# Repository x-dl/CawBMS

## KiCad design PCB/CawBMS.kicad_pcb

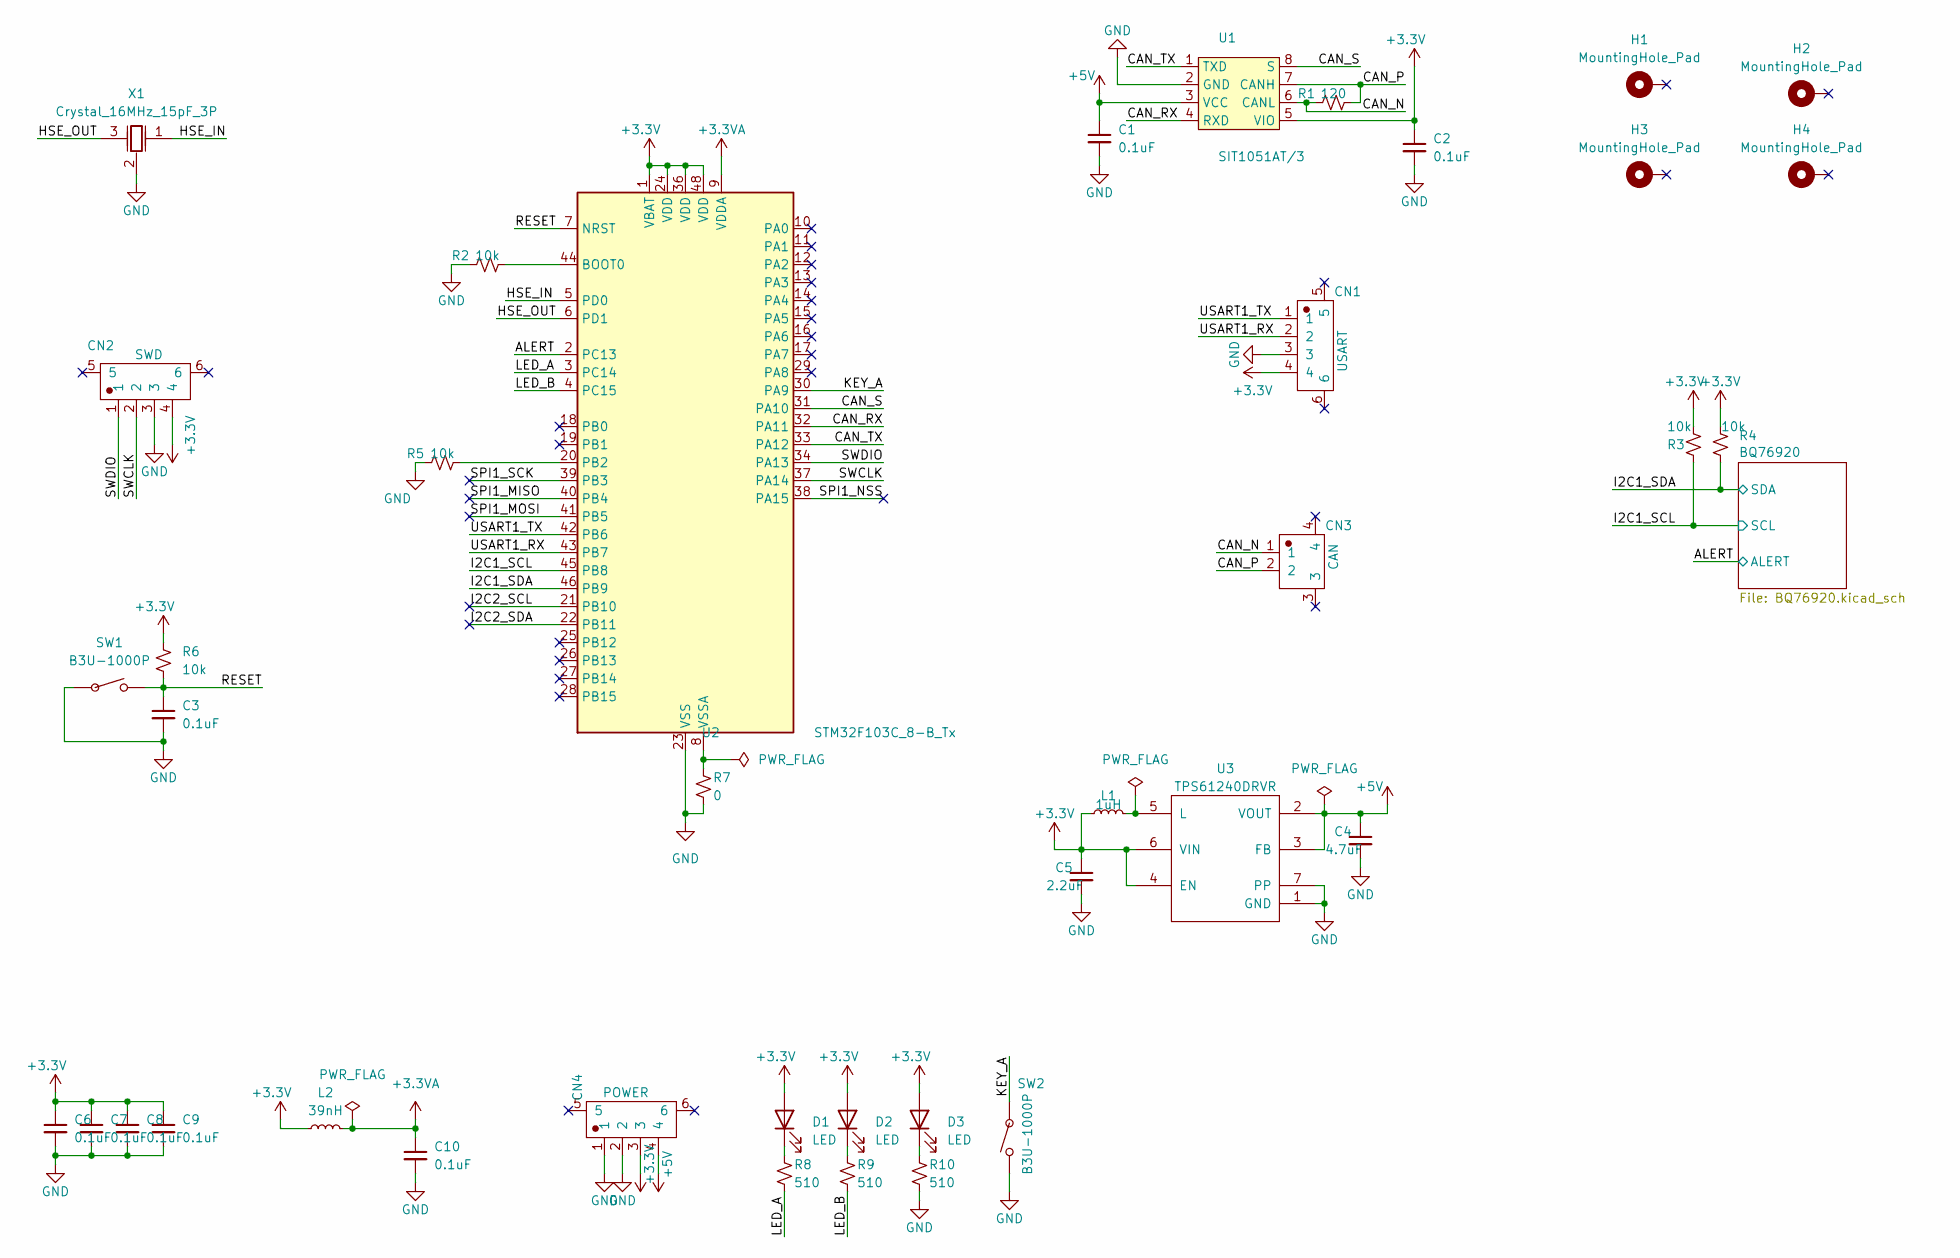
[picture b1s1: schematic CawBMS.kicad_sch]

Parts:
C1, C2, C3, C6, C7, C8, C9, C10: 0.1uF; C_0402_1005Metric_Pad0.74x0.62mm_HandSolder
C4: 4.7uF; C_0402_1005Metric_Pad0.74x0.62mm_HandSolder
C5: 2.2uF; C_0402_1005Metric_Pad0.74x0.62mm_HandSolder
CN1: USART; CONN-SMD_4P-P1.00_WAFER-SH1.0-4PWB
CN2: SWD; CONN-SMD_4P-P1.00_WAFER-SH1.0-4PWB
CN3: CAN; CONN-SMD_2P-P1.00_XUNPU_WAFER-SH1.0-2PWB
CN4: POWER; CONN-SMD_4P-P1.00_WAFER-SH1.0-4PWB
D1, D2, D3: LED; LED_0402_1005Metric_Pad0.77x0.64mm_HandSolder
H1, H2, H3, H4: MountingHole_Pad; MountingHole_2.2mm_M2_Pad_Via
L1: 1uH; L_1210_3225Metric_Pad1.42x2.65mm_HandSolder
L2: 39nH; L_0402_1005Metric_Pad0.77x0.64mm_HandSolder
R1: 120; R_0402_1005Metric_Pad0.72x0.64mm_HandSolder
R2, R3, R4, R5, R6: 10k; R_0402_1005Metric_Pad0.72x0.64mm_HandSolder
R7: 0; R_0402_1005Metric_Pad0.72x0.64mm_HandSolder
R8, R9, R10: 510; R_0402_1005Metric_Pad0.72x0.64mm_HandSolder
SW1, SW2: B3U-1000P; JLC Part Number C231329
U1: SIT1051AT/3; ISO1044BDR_SOP-8
U2: STM32F103C_8-B_Tx; LQFP-48_7x7mm_P0.5mm
U3: TPS61240DRVR; TPS61240DRVR_WSON-6_L2.0-W2.0-P0.65-TL-EP
X1: Crystal_16MHz_15pF_3P; Crystal_SMD3213-3P; JLC Part Number C341521

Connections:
+3.3V: C2.1, C5.1, C6.1, C7.1, C8.1, C9.1, CN1.4, CN2.4, CN4.3, D1.2 (A), D2.2 (A), D3.2 (A), L1.1, L2.1, R3.1, R4.1, R6.1, U1.5 (VIO), U2.1 (VBAT), U2.24 (VDD), U2.36 (VDD), U2.48 (VDD), U3.4 (EN), U3.6 (VIN); also elsewhere on the board
+3.3VA: C10.1, L2.2, U2.9 (VDDA)
+5V: C1.1, C4.1, CN4.4, U1.3 (VCC), U3.2 (VOUT), U3.3 (FB)
/ALERT: U2.2 (PC13); also elsewhere on the board
/CAN_N: CN3.1, R1.1, U1.6 (CANL)
/CAN_P: CN3.2, R1.2, U1.7 (CANH)
/CAN_RX: U1.4 (RXD), U2.32 (PA11)
/CAN_S: U1.8 (S), U2.31 (PA10)
/CAN_TX: U1.1 (TXD), U2.33 (PA12)
/HSE_IN: U2.5 (PD0), X1.1 (OSC1)
/HSE_OUT: U2.6 (PD1), X1.3 (OSC2)
/I2C1_SCL: R3.2, U2.45 (PB8); also elsewhere on the board
/I2C1_SDA: R4.2, U2.46 (PB9); also elsewhere on the board
/I2C2_SCL: U2.21 (PB10)
/I2C2_SDA: U2.22 (PB11)
/KEY_A: SW2.1, U2.30 (PA9)
/LED_A: R8.2, U2.3 (PC14)
/LED_B: R9.2, U2.4 (PC15)
/RESET: C3.1, R6.2, SW1.2, U2.7 (NRST)
/SPI1_MISO: U2.40 (PB4)
/SPI1_MOSI: U2.41 (PB5)
/SPI1_NSS: U2.38 (PA15)
/SPI1_SCK: U2.39 (PB3)
/SWCLK: CN2.2, U2.37 (PA14)
/SWDIO: CN2.1, U2.34 (PA13)
/USART1_RX: CN1.2, U2.43 (PB7)
/USART1_TX: CN1.1, U2.42 (PB6)
GND: C1.2, C2.2, C3.2, C4.2, C5.2, C6.2, C7.2, C8.2, C9.2, C10.2, CN1.3, CN2.3, CN4.1, CN4.2, R2.1, R5.1, R7.2, R10.2, SW1.1, SW2.2, U1.2 (GND), U2.23 (VSS), U2.35 (VSS), U2.47 (VSS), U3.1 (GND), U3.7 (PP), X1.2 (GND); also elsewhere on the board
unnamed: D1.1 (K), R8.1
unnamed: D2.1 (K), R9.1
unnamed: D3.1 (K), R10.1
unnamed: R2.2, U2.44 (BOOT0)
unnamed: R5.2, U2.20 (PB2)
unnamed: R7.1, U2.8 (VSSA)
unnamed: L1.2, U3.5 (L)

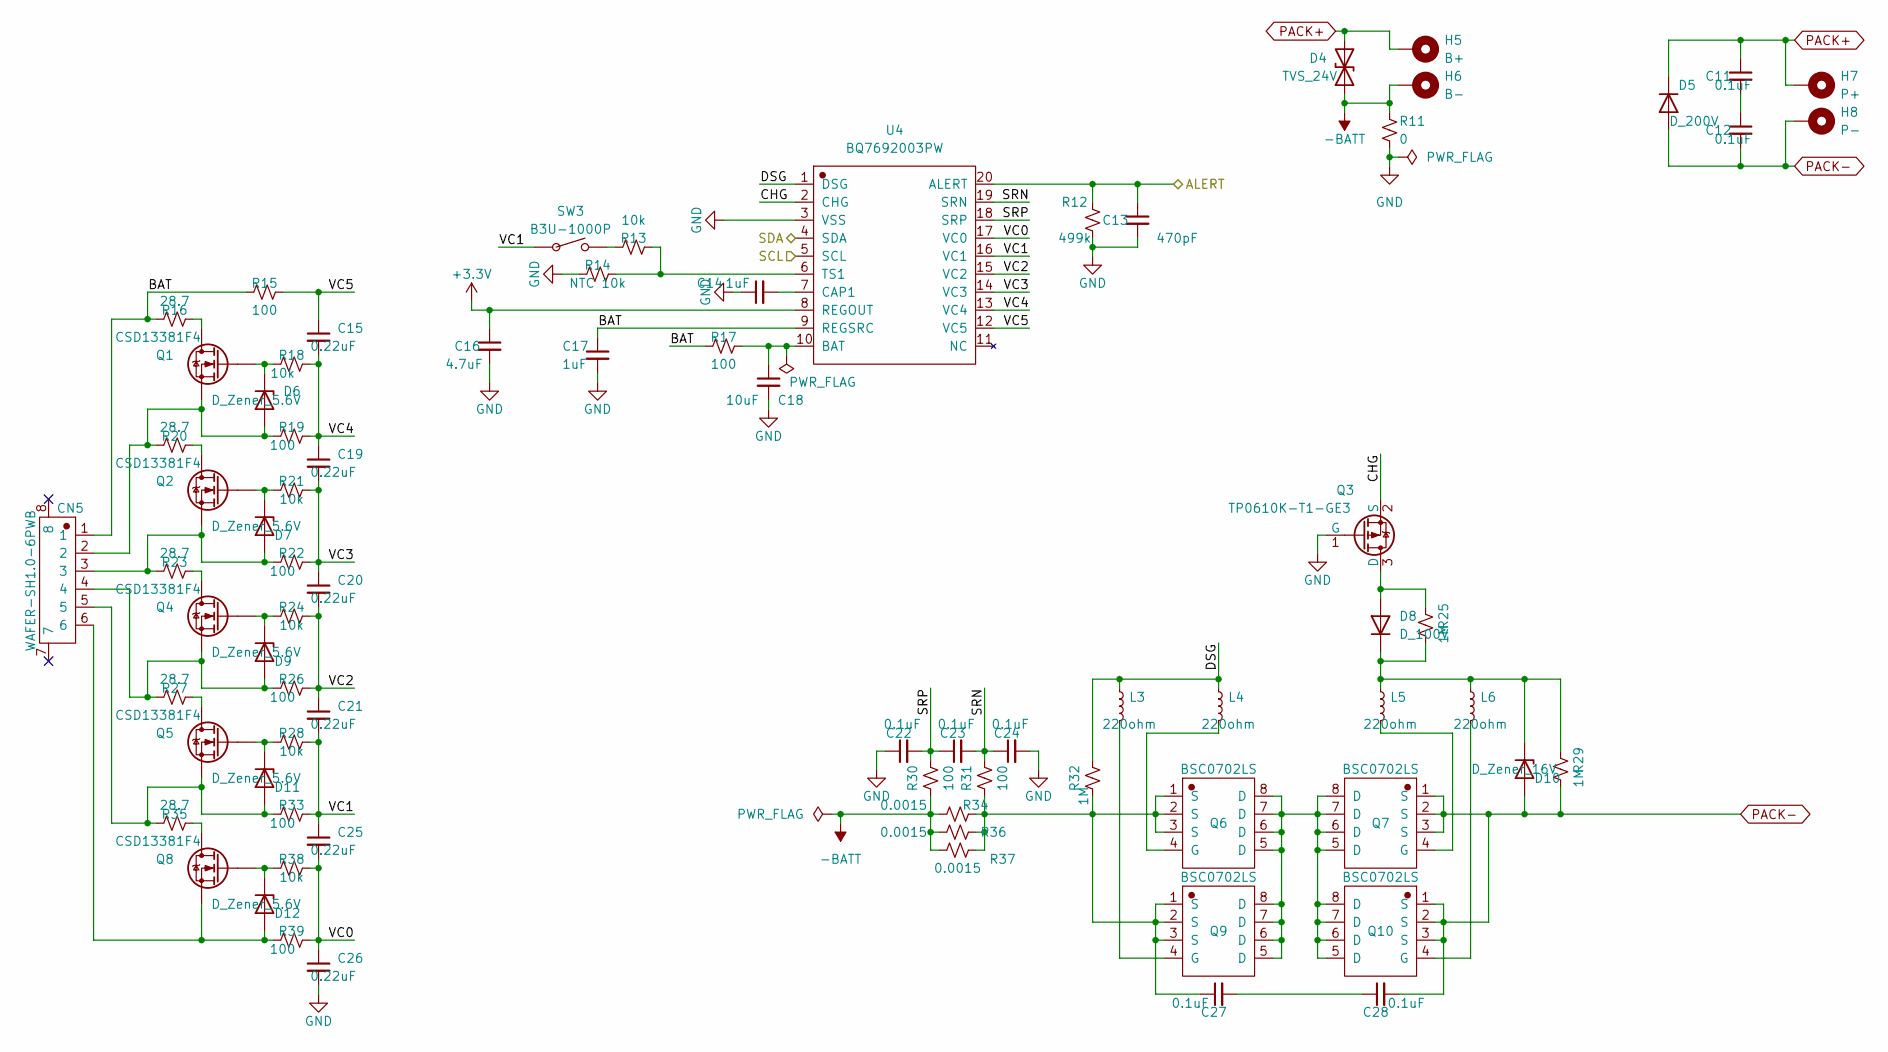
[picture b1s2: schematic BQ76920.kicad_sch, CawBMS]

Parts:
C11, C12, C27, C28: 0.1uF; C_0603_1608Metric_Pad1.08x0.95mm_HandSolder
C13: 470pF; C_0402_1005Metric_Pad0.74x0.62mm_HandSolder
C14, C17: 1uF; C_0402_1005Metric_Pad0.74x0.62mm_HandSolder
C15, C19, C20, C21, C25, C26: 0.22uF; C_0402_1005Metric_Pad0.74x0.62mm_HandSolder
C16: 4.7uF; C_0402_1005Metric_Pad0.74x0.62mm_HandSolder
C18: 10uF; C_0603_1608Metric_Pad1.08x0.95mm_HandSolder
C22, C23, C24: 0.1uF; C_0402_1005Metric_Pad0.74x0.62mm_HandSolder
CN5: WAFER-SH1.0-6PWB; CONN-SMD_6P-P1.00_XUNPU_WAFER-SH1.0-6PWB
D4: TVS_24V; D_SMA_Handsoldering
D5: D_200V; D_SMA_Handsoldering
D6, D7, D9, D11, D12: D_Zener_5.6V; D_SOD-523
D8: D_100V; D_SOD-323_HandSoldering
D10: D_Zener_16V; D_SOD-523
H5: B+; POWER_PAD
H6: B-; POWER_PAD
H7: P+; POWER_PAD
H8: P-; POWER_PAD
L3, L4, L5, L6: 220ohm; L_0603_1608Metric_Pad1.05x0.95mm_HandSolder
Q1, Q2, Q4, Q5, Q8: CSD13381F4; CSD13381F4_PICOSTAR-3_L1.0-W0.6-P0.40-S0.65-BL-1
Q3: TP0610K-T1-GE3; SOT-23
Q6, Q7, Q9, Q10: BSC0702LS; BSC0702LS_PG-TDSON-8_L5.0-W6.0-P1.27-BL-EP
R11: 0; R_0402_1005Metric_Pad0.72x0.64mm_HandSolder
R12: 499k; R_0402_1005Metric_Pad0.72x0.64mm_HandSolder
R13, R18, R21, R24, R28, R38: 10k; R_0402_1005Metric_Pad0.72x0.64mm_HandSolder
R14: NTC 10k; R_0402_1005Metric_Pad0.72x0.64mm_HandSolder
R15, R17, R19, R22, R26, R30, R31, R33, R39: 100; R_0402_1005Metric_Pad0.72x0.64mm_HandSolder
R16, R20, R23, R27, R35: 28.7; R_0402_1005Metric_Pad0.72x0.64mm_HandSolder
R25, R29, R32: 1M; R_0402_1005Metric_Pad0.72x0.64mm_HandSolder
R34, R36, R37: 0.0015; R_2512_6332Metric_Pad1.40x3.35mm_HandSolder
SW3: B3U-1000P; JLC Part Number C231329
U4: BQ7692003PW; BQ7692003PW_TSSOP-20_L6.5-W4.4-P0.65-LS6.4-BL

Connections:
+3.3V: C16.1, U4.8 (REGOUT); also elsewhere on the board
-BATT: D4.1 (A1), H6.1, R11.1, R30.1, R34.1, R36.1, R37.1
/ALERT: C13.1, R12.2, U4.20 (ALERT); also elsewhere on the board
/BQ76920/BAT: C17.1, CN5.1, R15.1, R16.1, R17.1, U4.9 (REGSRC)
/BQ76920/CHG: Q3.2 (S), U4.2 (CHG)
/BQ76920/DSG: L3.1, L4.1, R32.2, U4.1 (DSG)
/BQ76920/SRN: C23.2, C24.1, R31.2, U4.19 (SRN)
/BQ76920/SRP: C22.2, C23.1, R30.2, U4.18 (SRP)
/BQ76920/VC0: C25.2, C26.1, R38.2, R39.2, U4.17 (VC0)
/BQ76920/VC1: C21.2, C25.1, R28.2, R33.2, SW3.1, U4.16 (VC1)
/BQ76920/VC2: C20.2, C21.1, R24.2, R26.2, U4.15 (VC2)
/BQ76920/VC3: C19.2, C20.1, R21.2, R22.2, U4.14 (VC3)
/BQ76920/VC4: C15.2, C19.1, R18.2, R19.2, U4.13 (VC4)
/BQ76920/VC5: C15.1, R15.2, U4.12 (VC5)
/I2C1_SCL: U4.5 (SCL); also elsewhere on the board
/I2C1_SDA: U4.4 (SDA); also elsewhere on the board
GND: C13.2, C14.1, C16.2, C17.2, C18.2, C22.1, C24.2, C26.2, Q3.1 (G), R11.2, R12.1, R14.1, U4.3 (VSS); also elsewhere on the board
unnamed: C11.2, C12.1
unnamed: C27.1, Q6.1 (S), Q6.2 (S), Q6.3 (S), Q9.1 (S), Q9.2 (S), Q9.3 (S), R31.1, R32.1, R34.2, R36.2, R37.2
unnamed: C27.2, C28.1
unnamed: CN5.2, D6.2 (A), Q1.2 (S), R19.1, R20.1
unnamed: D6.1 (K), Q1.1 (G), R18.1
unnamed: CN5.3, D7.2 (A), Q2.2 (S), R22.1, R23.1
unnamed: D7.1 (K), Q2.1 (G), R21.1
unnamed: D8.2 (A), Q3.3 (D), R25.2
unnamed: CN5.4, D9.2 (A), Q4.2 (S), R26.1, R27.1
unnamed: D9.1 (K), Q4.1 (G), R24.1
unnamed: D8.1 (K), D10.1 (K), L5.1, L6.1, R25.1, R29.2
unnamed: CN5.5, D11.2 (A), Q5.2 (S), R33.1, R35.1
unnamed: D11.1 (K), Q5.1 (G), R28.1
unnamed: CN5.6, D12.2 (A), Q8.2 (S), R39.1
unnamed: D12.1 (K), Q8.1 (G), R38.1
unnamed: Q1.3 (D), R16.2
unnamed: Q2.3 (D), R20.2
unnamed: Q4.3 (D), R23.2
unnamed: Q5.3 (D), R27.2
unnamed: L4.2, Q6.4 (G)
unnamed: L5.2, Q7.4 (G)
unnamed: Q8.3 (D), R35.2
unnamed: L3.2, Q9.4 (G)
unnamed: Q6.5 (D), Q6.6 (D), Q6.7 (D), Q6.8 (D), Q7.5 (D), Q7.6 (D), Q7.7 (D), Q7.8 (D), Q9.5 (D), Q9.6 (D), Q9.7 (D), Q9.8 (D), Q10.5 (D), Q10.6 (D), Q10.7 (D), Q10.8 (D)
unnamed: L6.2, Q10.4 (G)
unnamed: R13.1, SW3.2
unnamed: C18.1, R17.2, U4.10 (BAT)
unnamed: C14.2, U4.7 (CAP1)
unnamed: R13.2, R14.2, U4.6 (TS1)
PACK+: C11.1, D4.2 (A2), D5.1 (K), H5.1, H7.1
PACK-: C12.2, C28.2, D5.2 (A), D10.2 (A), H8.1, Q7.1 (S), Q7.2 (S), Q7.3 (S), Q10.1 (S), Q10.2 (S), Q10.3 (S), R29.1

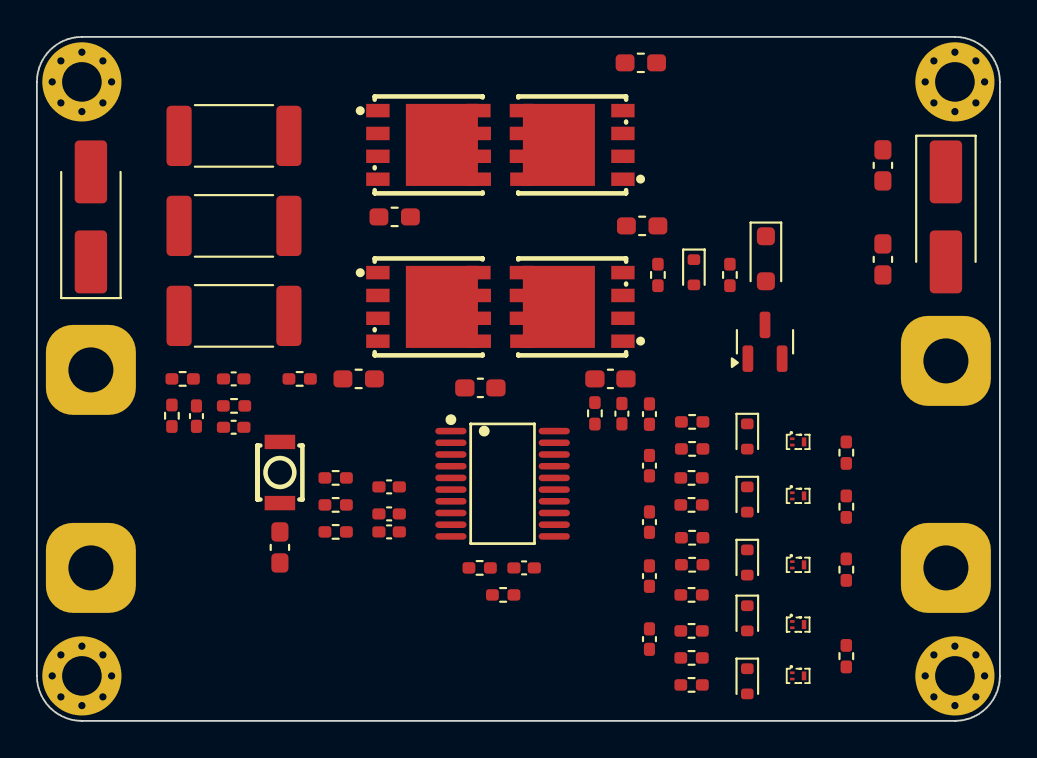
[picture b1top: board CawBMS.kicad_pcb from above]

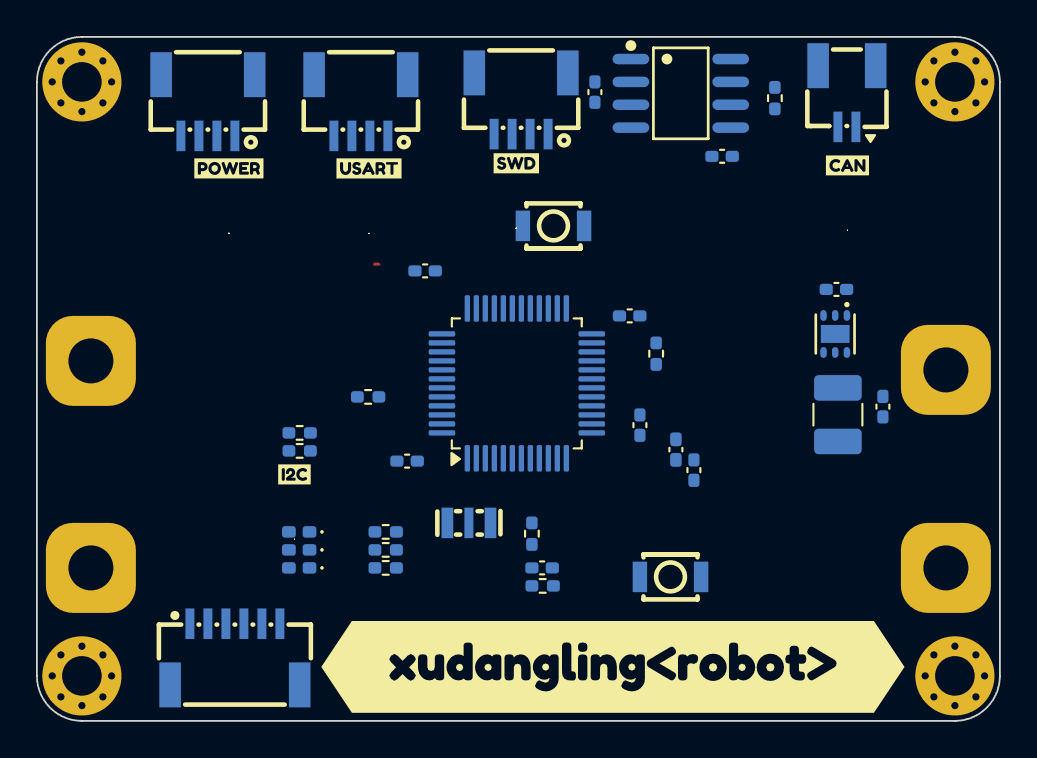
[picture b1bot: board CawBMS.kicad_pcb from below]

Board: 2 copper layers, 53.5 x 38.0 mm, 122 parts (42 on the bottom side), 72 nets.

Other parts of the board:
kibuzzard-67C7CF73: G***; kibuzzard-67C7CF73
kibuzzard-658FE662: G***; kibuzzard-658FE662
kibuzzard-658FE679: G***; kibuzzard-658FE679
kibuzzard-6577EBAB: G***; kibuzzard-6577EBAB
kibuzzard-6577EC0F: G***; kibuzzard-6577EC0F
kibuzzard-6577EC47: G***; kibuzzard-6577EC47

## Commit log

2025-02-23 xudangling initial commit
2025-03-05 3.5 布局完成
